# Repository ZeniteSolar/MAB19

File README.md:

# MCS19
**M**ódulo de **C**arregamento do **S**istema 2019  
Embarcação Guarapuvu II  
Equipe Zênite Solar  

### Sobre

Este módulo é responsável por gerenciar o carregamento do sistema com a finalidade de garantir segurança para a embarcação.

#### Requisitos e Abordagens
1. Gerenciar o acionamento das bombas de porão.
    - Ser controlado através da rede CAN da embarcação.
2. Isolamento eletrico entre a bateria auxiliar e  o resto do sistema
    - Utilizar de um optoacoplador para o acionamento dos reles

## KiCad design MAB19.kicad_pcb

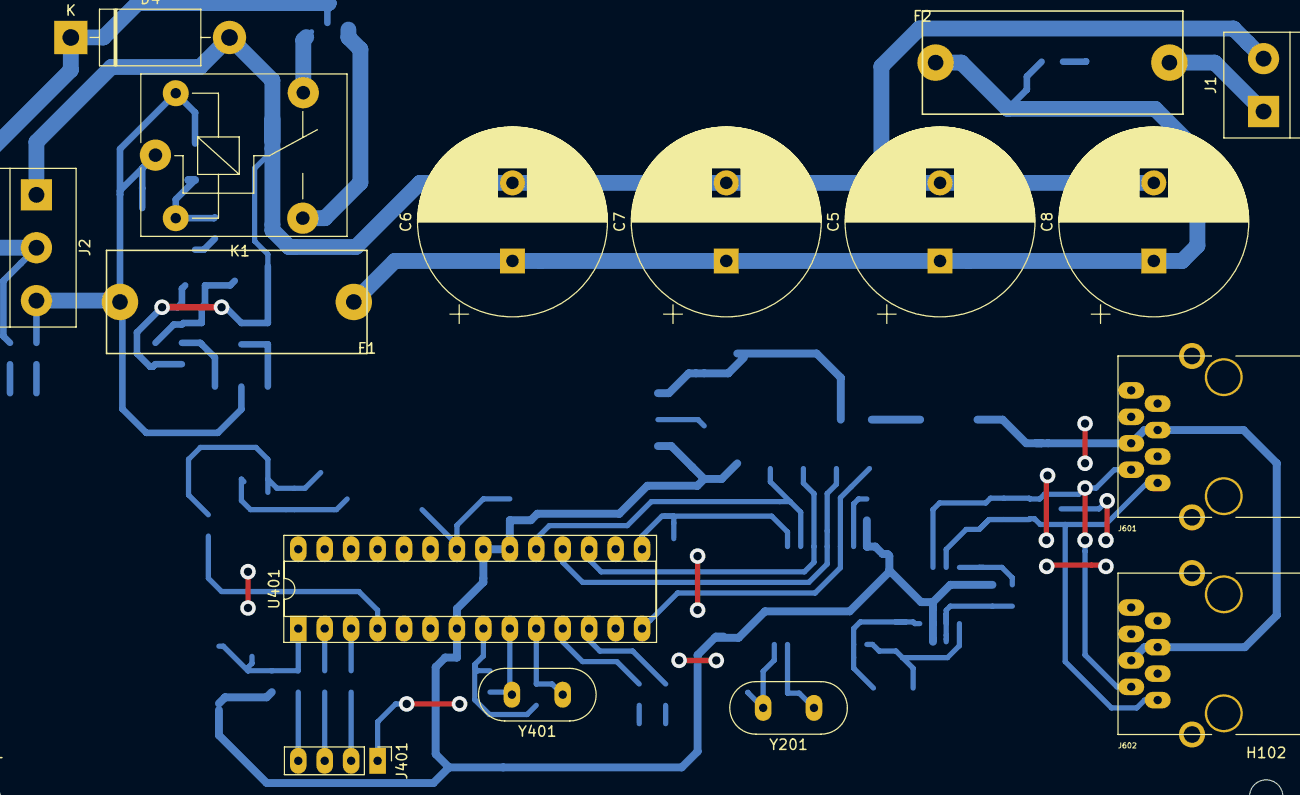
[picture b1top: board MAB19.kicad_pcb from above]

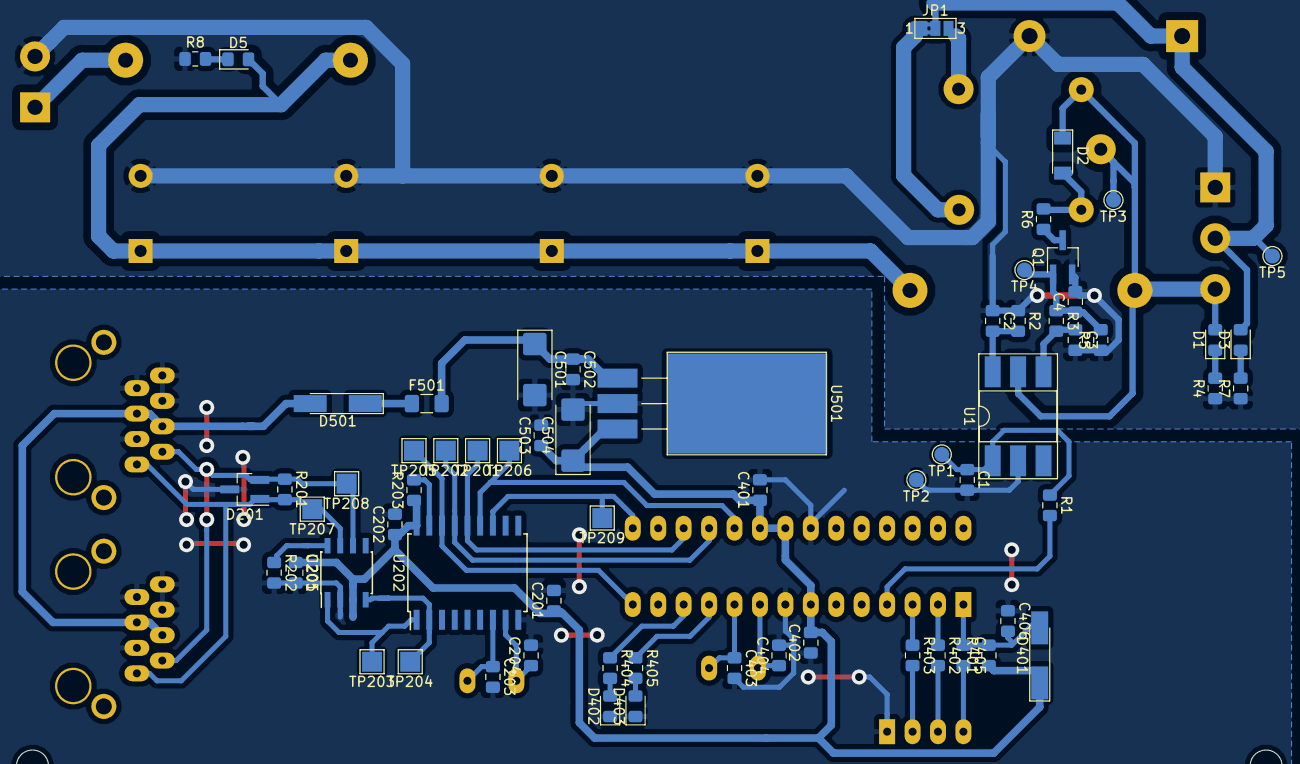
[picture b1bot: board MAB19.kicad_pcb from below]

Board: 2 copper layers, 85 parts (65 on the bottom side), 47 nets.

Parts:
C1, C3, C4: 100n; C_0805_2012Metric_Pad1.15x1.40mm_HandSolder
C2: 1n; C_0805_2012Metric_Pad1.15x1.40mm_HandSolder
C5, C6, C7, C8: 4700u 35V; CP_Radial_D18.0mm_P7.50mm
C201, C202, C205, C401, C402, C405, C406, C502, C503: 100nF; C_0805_2012Metric_Pad1.15x1.40mm_HandSolder
C203, C204, C403, C404: 22pF; C_0805_2012Metric_Pad1.15x1.40mm_HandSolder
C501, C504: 1uF; CP_EIA-6032-20_AVX-F_Pad2.25x2.35mm_HandSolder
D1, D5: G3mm; LED_0805_2012Metric_Pad1.15x1.40mm_HandSolder
D2: LL4148; D_MiniMELF
D3: R3mm; LED_0805_2012Metric_Pad1.15x1.40mm_HandSolder
D4: MUR460; D_DO-201AD_P15.24mm_Horizontal
D201: pesd1can; SOT-23_Handsoldering
D401, D501: LL4148; D_MiniMELF_Handsoldering
D402, D403: LED_RED; LED_0805_2012Metric_Pad1.15x1.40mm_HandSolder
F1: 3A; Fuse_Holder_5x20
F2: 10A; Fuse_Holder_5x20
F501: 500mA; Fuse_1206_3216Metric_Pad1.42x1.75mm_HandSolder
H101, H102, H103, H104: MountingHole; MountingHole_3.2mm_M3
J1: Screw_Terminal_01x02; TerminalBlock_bornier-2_P5.08mm
J2: Screw_Terminal_01x03; TerminalBlock_bornier-3_P5.08mm
J401: USART; PinHeader_1x04_P2.54mm_Vertical
J601, J602: RJ45; RJ45_YH59_01
JP1: SolderJumper_3_Bridged12; SolderJumper-3_P1.3mm_Bridged2Bar12_Pad1.0x1.5mm_NumberLabe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
K1: coil: 12VDC, contact: 125V/10A; Relay_SPDT_SANYOU_SRD_Series_Form_C
Q1: Q_NPN_BEC; TSOT-23_HandSoldering
R1: 330R; R_0805_2012Metric_Pad1.15x1.40mm_HandSolder
R2: NC; R_0805_2012Metric_Pad1.15x1.40mm_HandSolder
R3: 1k2; R_0805_2012Metric_Pad1.15x1.40mm_HandSolder
R4, R7, R8, R402, R403, R404, R405: 1k; R_0805_2012Metric_Pad1.15x1.40mm_HandSolder
R5, R203, R401: 10k; R_0805_2012Metric_Pad1.15x1.40mm_HandSolder
R6: 120R; R_0805_2012Metric_Pad1.15x1.40mm_HandSolder
R201: 120; R_0805_2012Metric_Pad1.15x1.40mm_HandSolder
R202: 4k7; R_0805_2012Metric_Pad1.15x1.40mm_HandSolder
TP1: A1; TestPoint_Pad_D1.5mm
TP2: K1; TestPoint_Pad_D1.5mm
TP3: 12V; TestPoint_Pad_D1.5mm
TP4: B1; TestPoint_Pad_D1.5mm
TP5: OUT1; TestPoint_Pad_D1.5mm
TP201: SI; TestPoint_Pad_2.0x2.0mm
TP202: SO; TestPoint_Pad_2.0x2.0mm
TP203: TXCAN; TestPoint_Pad_2.0x2.0mm
TP204: RXCAN; TestPoint_Pad_2.0x2.0mm
TP205: SC; TestPoint_Pad_2.0x2.0mm
TP206: SCK; TestPoint_Pad_2.0x2.0mm
TP207: CAN_H; TestPoint_Pad_2.0x2.0mm
TP208: CAN_L; TestPoint_Pad_2.0x2.0mm
TP209: INT; TestPoint_Pad_2.0x2.0mm
U1: 4N25; DIP-6_W8.89mm_SMDSocket_LongPads
U201: MCP2551-I/SN; SOIC-8_3.9x4.9mm_P1.27mm
U202: MCP2515-xSO; SOIC-18W_7.5x11.6mm_P1.27mm
U401: ATMEGA328P-PU; DIP-28_W7.62mm_Socket
U501: LM7805; TO-220-3_Horizontal_TabDown_SMD
Y201, Y401: 16MHz; Crystal_HC49-U_Vertical

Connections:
+5V: C201.1, C202.1, C205.1, C401.1, C402.2, C503.1, C504.1, D401.1, R203.1, R401.1, U201.3, U202.18, U401.7, U401.20, U401.21, U501.3
+12V: C5.1, C6.1, C7.1, C8.1, D5.2, F1.1, F2.1
/CANBUS CONN/CAN_H: D201.1, J601.1, J602.1, R201.2, TP207.1, U201.7
/CANBUS CONN/CAN_L: D201.2, J601.2, J602.2, R201.1, TP208.1, U201.6
/CANBUS/CS: TP205.1, U202.16, U401.14
/CANBUS/INT: TP209.1, U202.12, U401.15
/CANBUS/RXCAN: TP204.1, U201.4, U202.2
/CANBUS/TXCAN: TP203.1, U201.1, U202.1
/MCU/LED1: R405.1, U401.11
/MCU/LED2: R404.1, U401.12
/MCU/ON_OFF_PUMP: R1.2, U401.4
/MCU/RESET: C405.1, C406.2, D401.2, R401.2, U401.1
/MCU/USART_RX: R402.1, U401.2
/MCU/USART_TX: R403.1, U401.3
/MISO: TP202.1, U202.15, U401.18
/MOSI: TP201.1, U202.14, U401.17
/POWER SUPPLY/+18V_IN: D501.2, J601.4, J601.5, J602.4, J602.5
/SCK: TP206.1, U202.13, U401.19
/filter/Vin: F2.2, J1.1
/pump_driver/+Pump: D3.2, D4.1, J2.2, JP1.2, TP5.1
/pump_driver/Level_sensor: D1.2, D2.1, F1.2, J2.3, K1.1, K1.5, TP3.1, U1.5
GND: C1.2, C201.2, C202.2, C203.2, C204.2, C205.2, C401.2, C402.1, C403.2, C404.2, C406.1, C501.2, C502.2, C503.2, C504.2, D201.3, D402.1, D403.1, J401.1, J601.3, J601.6, J601.7, J601.8, J602.3, J602.6, J602.7, J602.8, R202.2, TP2.1, U1.2, U201.2, U202.9, U401.8, U401.22, U501.2
GNDPWR: C2.1, C3.2, C4.2, C5.2, C6.2, C7.2, C8.2, D4.2, J1.2, J2.1, Q1.2, R2.1, R4.1, R5.1, R7.1, R8.1
unnamed: C1.1, R1.1, TP1.1, U1.1
unnamed: C2.2, R2.2, U1.6
unnamed: C3.1, R3.2, U1.4
unnamed: C4.1, Q1.1, R3.1, R5.2, TP4.1
unnamed: C203.1, U202.7, Y201.1
unnamed: C204.1, U202.8, Y201.2
unnamed: C403.1, U401.10, Y401.1
unnamed: C404.1, U401.9, Y401.2
unnamed: C405.2, J401.4
unnamed: C501.1, C502.1, F501.2, U501.1
unnamed: D1.1, R4.2
unnamed: D2.2, K1.2, R6.2
unnamed: D3.1, R7.2
unnamed: D5.1, R8.2
unnamed: D402.2, R404.2
unnamed: D403.2, R405.2
unnamed: D501.1, F501.1
unnamed: J401.2, R403.2
unnamed: J401.3, R402.2
unnamed: JP1.1, K1.3
unnamed: JP1.3, K1.4
unnamed: Q1.3, R6.1
unnamed: R202.1, U201.8
unnamed: R203.2, U202.17

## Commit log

2019-03-18 Importados os esquematicos do MAB18 para o projeto do MCS19 para usar o can e uC
2019-03-18 Adicionado safe zone para separar os GNDs
2019-03-18 Pequena alteeração
2019-03-19 First version PCB
2019-03-19 Foram reorganizadas algumas zonas para diminuir as dimensoes
2019-03-19 Foram reposicionados os conectores Pois onde eles estavam não permitiam que ouvese uma placa igual do lado
2019-03-23 Create LICENSE
2019-03-28 Solucionado erro na disposição dos pinos do BCV27
2019-04-29 Organização dos arquivos
2019-07-31 basic firmware, tested only with MIC17
2019-08-02 funcionando com o MIC19
2019-08-02 FIXED can_app_extractor_mic17_pumps
2020-01-19 reorganized, 3d exported
2020-01-20 avr-can-lib updated
2020-01-20 can_ids removed, makelibs updated
2020-01-20 makelibs updated
2020-01-20 updating MAB CAN messages
2020-01-21 updating MAM and GENERIC CAN messages
2020-01-21 mask added to conf.h
2020-02-14 .gitignore updated
2020-07-13 Export 3D ans layout images
2020-07-19 clone of MAB19
2020-07-19 gitignore
2020-07-19 Revert "gitignore"
    This reverts commit e70b843413eae7443d92e3db1b3329385fe013be.
2020-07-19 Revert "clone of MAB19"
    This reverts commit 65590e10a33a90435167e6ac9149648b248fbad7.
